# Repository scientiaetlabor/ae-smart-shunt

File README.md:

<h1 align="center">

  Ace's Electronics Pty Ltd  
  Smart Battery Shunt
</h1>

# Looking to get up and running?
- [Wiki - Quickstart Guide](../../wiki/Quickstart-Guide)

# Project Goals:
The overall goal of this project is to make a simple, robust and reliable Ssmart batery shunt to monitor voltage, current and power of a lithium battery, or battery system.

# Design goals:  
- Smallest form-factor possible while being able to handle large currents, upwards of 300A, without getting too hot
- Zero maintenance
- Allow the data to be accessed from an OLED gauge, via BLE or ESPNow

# Features
- **High-Precision Monitoring**: Measures battery voltage, current, and power, and calculates state-of-charge (SOC).
- **Persistent State**: Remembers battery capacity and calibration settings across power cycles.
- **ESP-NOW Broadcasting**: Transmits battery data wirelessly to other ESP devices.
- **Heartbeat LED**: A blinking LED provides a visual indication that the device is running.
- **Load Disconnect Control**: Includes an onboard MOSFET driver to disconnect the load in case of a fault.
- **Comprehensive Protection Suite**:
    - **Low-Voltage Disconnect**: Protects the battery from over-discharge. The device enters a low-power sleep mode, periodically waking to check if the battery has been recharged.
    - **Overcurrent Protection**: Disconnects the load if the current exceeds a configurable threshold.
    - **Short-Circuit Protection**: Uses the INA226's hardware alert pin for a fast-acting response to short circuits.
- **User-Configurable**: All protection parameters can be configured via the serial CLI.
- **In-Situ Calibration & Testing**: A guided CLI allows for accurate calibration and hardware verification without needing to re-flash the firmware.

# Commissioning
Before its first use, the smart shunt **must be calibrated**. The device will not be fully operational until this step is complete.
1.  Connect the device to a computer via USB.
2.  Open a serial monitor (e.g., the PlatformIO Serial Monitor) at **115200 baud**.
3.  Follow the on-screen prompts to run the calibration routines. You will be prompted to run the **Shunt Resistance Calibration (`r`)** first.
4.  Once calibration is complete, the device is ready for use.

# Serial Command-Line Interface (CLI)
The smart shunt is configured via a simple serial command-line interface. When connected, you can press a key followed by Enter to activate a command.

| Key | Command | Description |
|:---:|---|---|
| `c` | **Current Calibration** | Runs the guided multi-point current calibration routine. This maps the sensor's raw readings to true current values. |
| `r` | **Shunt Resistance Calibration** | Runs a routine to calculate the precise resistance of your shunt. **This must be run before first use.** |
| `p` | **Protection Settings** | Allows you to configure the thresholds for Low-Voltage Cutoff, Hysteresis, and Overcurrent Protection. |
| `l` | **Load Toggle** | Manually toggles the load disconnect MOSFET ON or OFF. Useful for testing the hardware circuit. |
| `a` | **Alert Toggle** | Toggles the hardware overcurrent alert ON or OFF. Useful for debugging. |
| `s` | **Status Display** | Displays the current protection settings, including the actual hardware alert threshold read from the INA226. |
| `d` | **Register Dump** | Prints the raw values of the INA226's key hardware registers for deep debugging. |

# v0.0.1
Version 0.0.1 has been prototyped. I will hand assemble some test boards and do some testing. ~ETA for completion is 10/8/25.

# Where to Buy:
TBA, but most likely will be vvailable to purchase in Australia or New Zealand via <a href="https://d1b959-f7.myshopify.com/">The AE Store</a>

## Support:
Contact me direct via ace<@>aceselectronics.com.au, just make it look like a normal email address. (hiding from the bots ;)

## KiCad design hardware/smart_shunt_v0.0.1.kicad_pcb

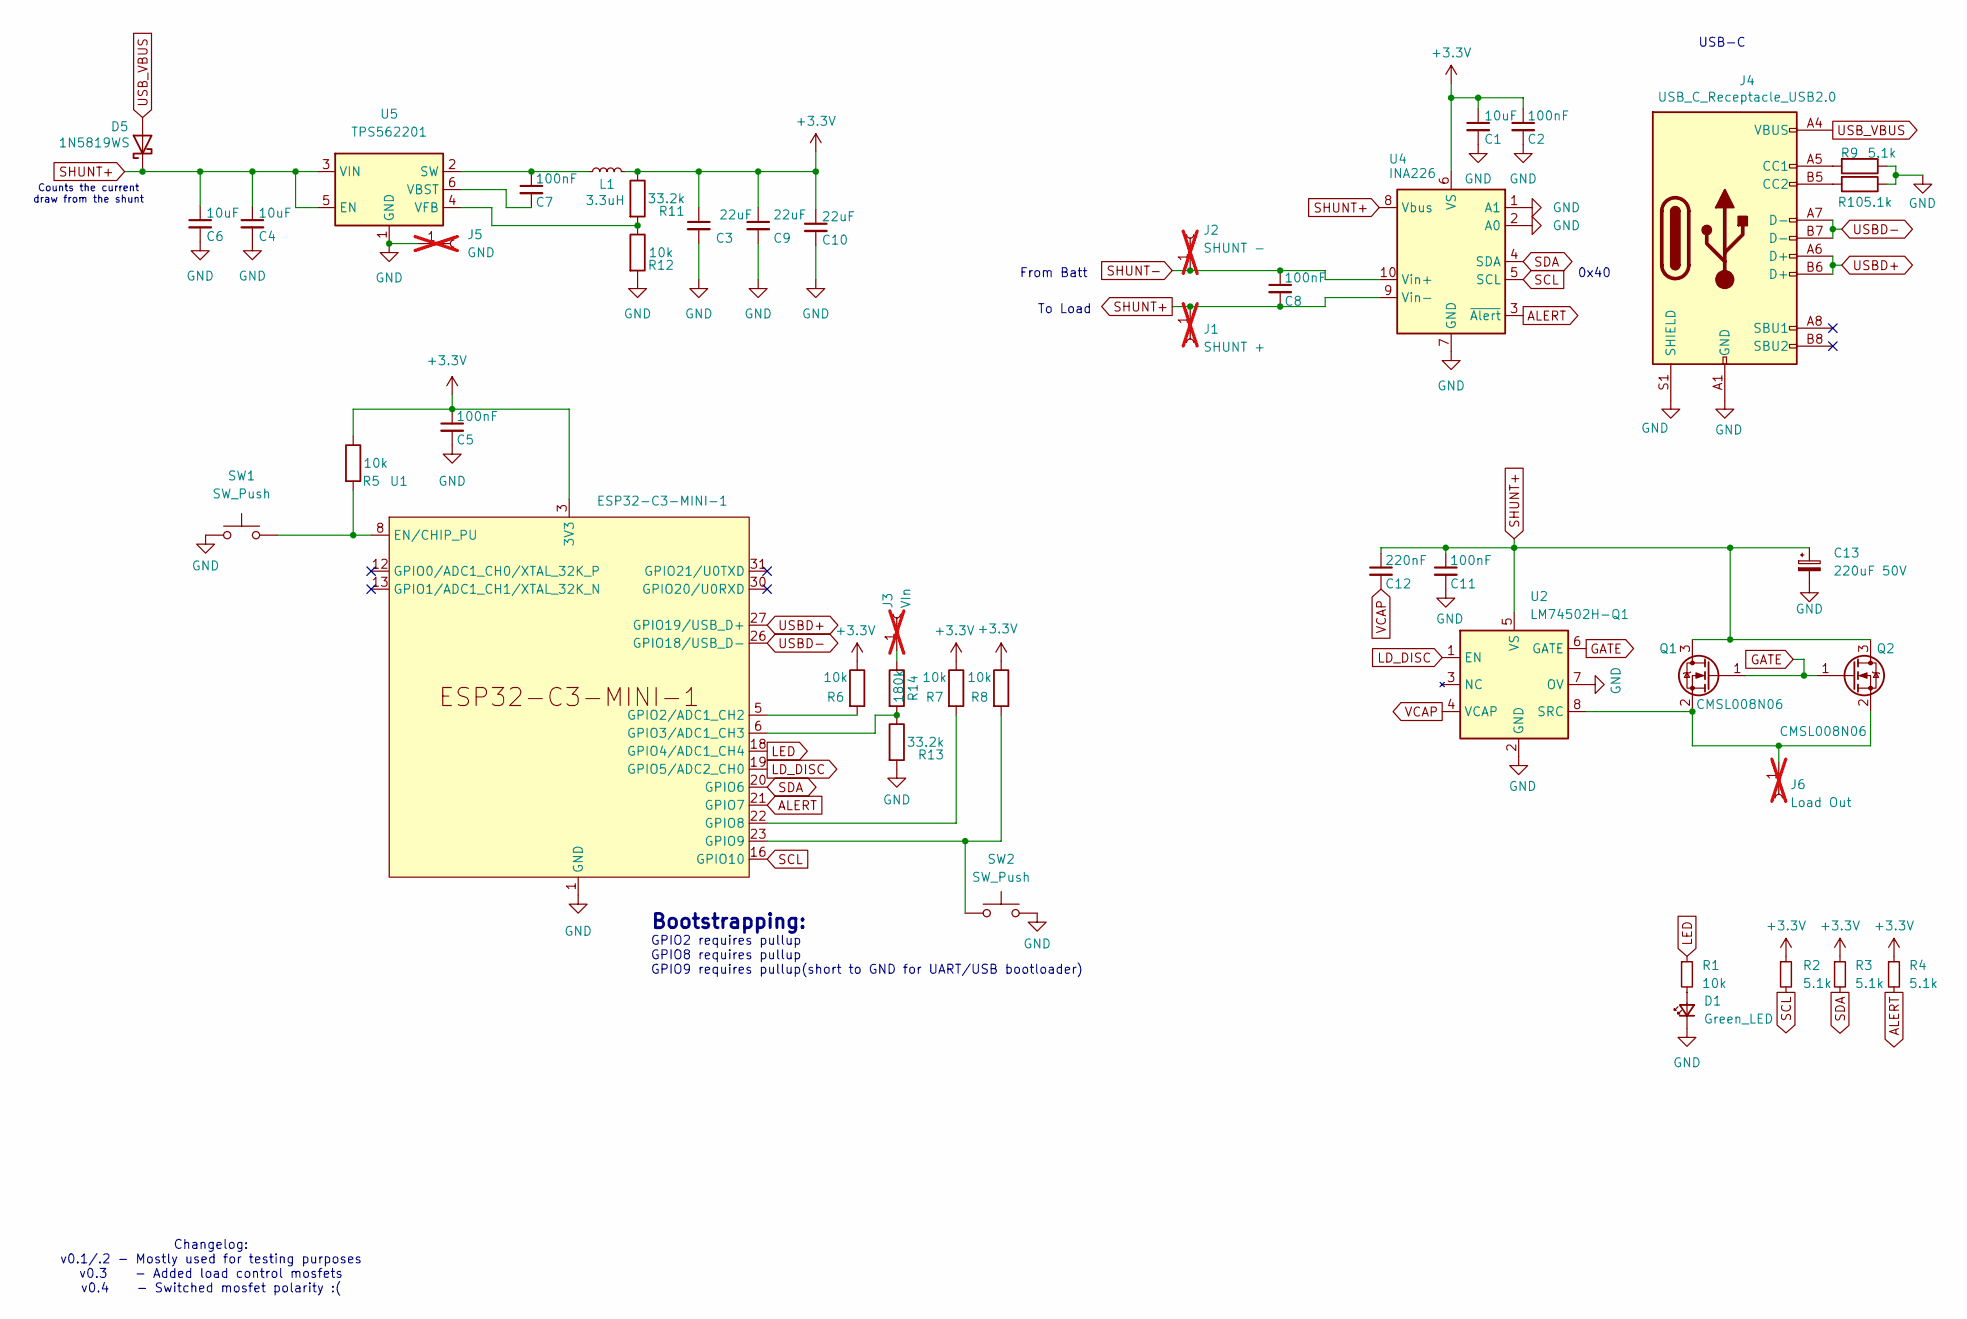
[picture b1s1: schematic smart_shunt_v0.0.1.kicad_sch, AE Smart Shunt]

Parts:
C1: 10uF; C_0603_1608Metric; MFR# CL10A106KP8NNNC; lcsc C19702
C2, C5, C7, C8, C11: 100nF; C_0603_1608Metric; MFR# CC0603KRX7R9BB104; lcsc C14663
C3, C9, C10: 22uF; C_0603_1608Metric; MFR# CL21A226MAQNNNE; lcsc C45783
C4, C6: 10uF; C_0805_2012Metric; MFR# GRM21BR6YA106KE43L; lcsc C162422
C12: 220nF; C_0805_2012Metric; MFR# CL21B224KBFNNNE; lcsc C5378
C13: 220uF 50V; CP_Elec_8x10.5; MFR# VP1H221M0810; lcsc C4054388
D1: Green_LED; LED_0402_1005Metric; MFR# SZYY0402YG; lcsc C434449
D5: 1N5819WS; D_SOD-323; MFR# 1N5819WS S4; lcsc C2927280
J1: SHUNT +; MountingHole_17mm; not fitted
J2: SHUNT -; MountingHole_17mm; not fitted
J3: VIn; MountingHole_3.2mm_M3_Pad_Via; not fitted
J4: USB_C_Receptacle_USB2.0; USB_C_Receptacle_GCT_USB4110; MFR# TYPE-C 16P QTWT; LCSC C5187472
J5: GND; MountingHole_3.2mm_M3_Pad_Via; not fitted
J6: Load Out; MountingHole_17mm; not fitted
L1: 3.3uH; L_APV_ANR4030; MFR# SWPA4030S3R3MT; lcsc C15269
Q1, Q2: CMSL008N06; MFR# CMSL008N06; lcsc C22364968
R1, R5, R6, R7, R8, R12: 10k; R_0603_1608Metric; MFR# 0603WAF1002T5E; lcsc C25804
R2, R3, R4, R9, R10: 5.1k; R_0603_1608Metric; MFR# 0603WAF5101T5E; lcsc C23186
R11, R13: 33.2k; R_0603_1608Metric; MFR# RMC060333.2K1%N; lcsc C325687
R14: 180k; R_0603_1608Metric; MFR# RC0603FR-07180KL; lcsc C123419
SW1, SW2: SW_Push; ALPSALPINE-SKSCLBE010_C115361; MFR# SKSCLBE010; lcsc C115361
U1: ESP32-C3-MINI-1; MFR# ESP32-C3-MINI-1-H4; lcsc C2934569
U2: LM74502H-Q1; SOT-23-8; MFR# TI LM74502HQDDFRQ1; lcsc C5219203
U4: INA226; VSSOP-10_3x3mm_P0.5mm; MFR# INA226AIDGSR; lcsc C49851
U5: TPS562201; SOT-23-6; MFR# TPS562201DDCR; lcsc C90061

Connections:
+3.3V: C1.1, C2.1, C3.1, C5.1, C9.1, C10.1, L1.2, R2.1, R3.1, R4.1, R5.1, R6.1, R7.1, R8.1, R11.1, U1.3 (3V3), U4.6 (VS)
ALERT: R4.2, U1.21 (GPIO7), U4.3 (~Alert)
GATE: Q1.1 (G), Q2.1 (G), U2.6 (GATE)
GND: C1.2, C2.2, C3.2, C4.2, C5.2, C6.2, C9.2, C10.2, C11.2, C13.2, D1.1 (K), J4.A1 (GND), J4.A12 (GND), J4.B1 (GND), J4.B12 (GND), J4.S1 (SHIELD), J5.1, R9.1, R10.1, R12.2, R13.2, SW1.2, SW2.2, U1.1 (GND), U1.2 (GND), U1.11 (GND), U1.14 (GND), U1.36 (GND), U1.37 (GND), U1.38 (GND), U1.39 (GND), U1.40 (GND), U1.41 (GND), U1.42 (GND), U1.43 (GND), U1.44 (GND), U1.45 (GND), U1.46 (GND), U1.47 (GND), U1.48 (GND), U1.49 (GND), U1.50 (GND), U1.51 (GND), U1.52 (GND), U1.53 (GND), U2.2 (GND), U2.7 (OV), U4.1 (A1), U4.2 (A0), U4.7 (GND), U5.1 (GND)
LD_DISC: U1.19 (GPIO5/ADC2_CH0), U2.1 (EN)
LED: R1.1, U1.18 (GPIO4/ADC1_CH4)
unnamed: D1.2 (A), R1.2
unnamed: J3.1, R14.1
unnamed: J4.A5 (CC1), R9.2
unnamed: J4.B5 (CC2), R10.2
unnamed: J6.1, Q1.2 (S), Q2.2 (S), U2.8 (SRC)
unnamed: R5.2, SW1.1, U1.8 (EN/CHIP_PU)
unnamed: R6.2, U1.5 (GPIO2/ADC1_CH2)
unnamed: R13.1, R14.2, U1.6 (GPIO3/ADC1_CH3)
unnamed: R7.2, U1.22 (GPIO8)
unnamed: R8.2, SW2.1, U1.23 (GPIO9)
unnamed: C7.1, L1.1, U5.2 (SW)
unnamed: C7.2, U5.6 (VBST)
unnamed: R11.2, R12.1, U5.4 (VFB)
SCL: R2.2, U1.16 (GPIO10), U4.5 (SCL)
SDA: R3.2, U1.20 (GPIO6), U4.4 (SDA)
SHUNT+: C4.1, C6.1, C8.2, C11.1, C12.1, C13.1, D5.1 (K), J1.1, Q1.3 (D), Q2.3 (D), U2.5 (VS), U4.8 (Vbus), U4.9 (Vin-), U5.3 (VIN), U5.5 (EN)
SHUNT-: C8.1, J2.1, U4.10 (Vin+)
USBD+: J4.A6 (D+), J4.B6 (D+), U1.27 (GPIO19/USB_D+)
USBD-: J4.A7 (D-), J4.B7 (D-), U1.26 (GPIO18/USB_D-)
USB_VBUS: D5.2 (A), J4.A4 (VBUS), J4.A9 (VBUS), J4.B4 (VBUS), J4.B9 (VBUS)
VCAP: C12.2, U2.4 (VCAP)

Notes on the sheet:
0x40
USB-C
From Batt
Counts the current draw from the shunt
Changelog: v0.1/.2 - Mostly used for testing purposes v0.3 - Added load control mosfets v0.4 - Switched mosfet polarity :(
To Load
Bootstrapping:
GPIO2 requires pullup GPIO8 requires pullup GPIO9 requires pullup(short to GND for UART/USB bootloader)

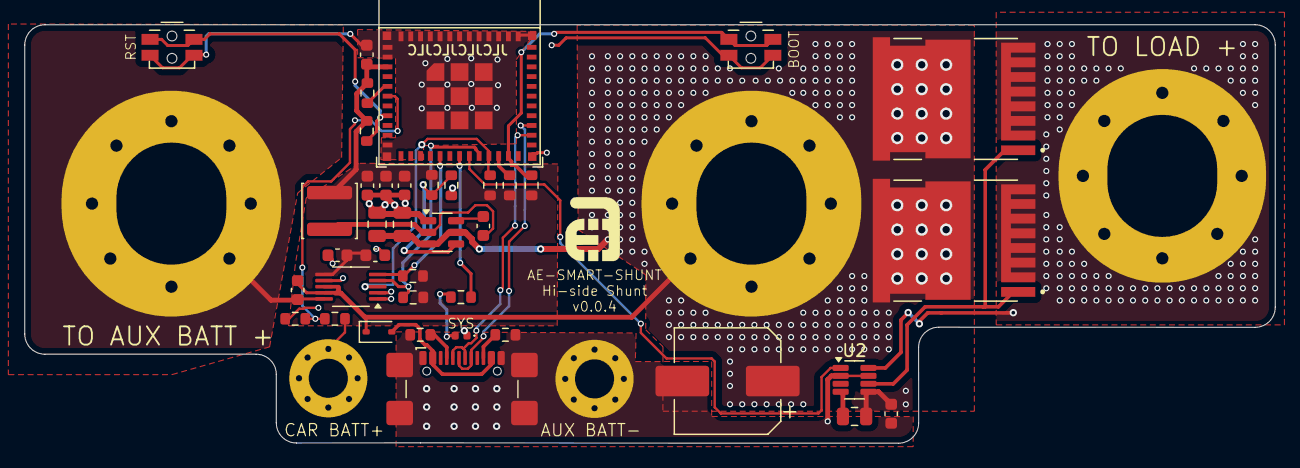
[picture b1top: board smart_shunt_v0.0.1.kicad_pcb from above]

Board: 2 copper layers, 102.4 x 34.3 mm, 44 parts (0 on the bottom side), 27 nets.

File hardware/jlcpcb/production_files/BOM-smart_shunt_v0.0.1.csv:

Comment,Designator,Footprint,LCSC,Quantity
SW_Push,"SW1,SW2",ALPSALPINE-SKSCLBE010_C115361,C115361,2
180k,R14,R_0603_1608Metric,C123419,1
100nF,"C11,C2,C5,C7,C8",C_0603_1608Metric,C14663,5
3.3uH,L1,L_APV_ANR4030,C15269,1
10uF,"C4,C6",C_0805_2012Metric,C15850,2
10uF,C1,C_0603_1608Metric,C19702,1
CMSL008N06,"Q1,Q2",CMSL008N06,C22364968,2
5.1k,"R10,R2,R3,R4,R9",R_0603_1608Metric,C23186,5
10k,"R1,R12,R5,R6,R7,R8",R_0603_1608Metric,C25804,6
ESP32-C3-MINI-1,U1,ESP32-C3-MINI-1,C2838502,1
1N5819WS,D5,D_SOD-323,C2927280,1
33.2k,"R11,R13",R_0603_1608Metric,C325687,2
Green_LED,D1,LED_0402_1005Metric,C401111,1
220uF 50V,C13,CP_Elec_8x10.5,C4054388,1
INA226,U4,VSSOP-10_3x3mm_P0.5mm,C49851,1
USB_C_Receptacle_USB2.0,J4,USB_C_Receptacle_GCT_USB4110,C5187472,1
LM74502H-Q1,U2,SOT-23-8,C5219203,1
220nF,C12,C_0805_2012Metric,C5378,1
22uF,"C10,C3,C9",C_0603_1608Metric,C59461,3
TPS562201,U5,SOT-23-6,C90061,1
SHUNT +,,MountingHole_17mm,,0
GND,,MountingHole_3.2mm_M3_Pad_Via,,0
SHUNT -,,MountingHole_17mm,,0
VIn,,MountingHole_3.2mm_M3_Pad_Via,,0
Load Out,,MountingHole_17mm,,0

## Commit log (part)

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2025-07-20 v0.0.1 off to JLCPCB
2025-07-20 cleaning up old files
2025-07-29 INA226 wip
2025-07-31 modifying project structure
2025-08-13 fixing RFT
2025-08-15 Updated RFT and calibration
2025-08-15 Fixing spaces
2025-08-16 feat: Add comprehensive test suite for firmware
    This change introduces a comprehensive test suite for the firmware.
    It adds a native test environment to allow for unit testing on a host machine.
    This required creating mocks for various Arduino and ESP-IDF libraries.
    The test suite covers:
    - Current, voltage, and power calculations.
    - Battery capacity and run-flat time calculations.
2025-08-16 feat: Add GitHub Actions workflow for CI
    This adds a GitHub Actions workflow to automatically run the native
    unit test suite on every push. This will help ensure code quality
    and prevent regressions.
2025-08-17 library updates
2025-08-17 feat: Add CI workflow for OTA releases
    This commit updates the CI workflow to automatically build the firmware and create a GitHub release when a new version tag is pushed.
    This is a necessary step for the OTA update functionality to work, as the device needs to download the `firmware.bin` from a GitHub release.
2025-08-17 Fixing ota stuff
2025-08-17 small fixes
2025-08-17 Testing OTA changes
2025-08-17 fixing missing variables
2025-08-17 Adding resistance calibration
2025-08-17 Changing logging
2025-08-29 v0.0.2 update, before FETs
2025-09-09 feat: Implement load protection and sleep features
    This commit introduces several new features to the smart shunt firmware:
    - **Load Disconnect Control:** The firmware can now control a load-disconnect MOSFET connected to GPIO5. The load is disconnected if the battery voltage or current go outside of user-defined ranges.
    - **Short-Circuit/Overcurrent Protection:** The INA226 alert pin, connected to GPIO7, is used to trigger an interrupt in case of a short circuit or overcurrent event. This provides a fast-acting prot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
    - **Low-Voltage Cutoff with Deep Sleep:** When the battery voltage drops below a configurable threshold, the load is di
2025-09-09 fix: Prevent deep sleep on USB power
    This commit fixes an issue where the device would enter deep sleep when powered from USB for setup, due to the low voltage protection being triggered by a low voltage reading when no battery is conne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
    The `checkAndHandleProtection` function is modified to bypass the low-voltage protection logic if the measured voltage is below 5.25V.
    A new unit test is added to verify this behavior.
2025-09-09 fix: Refactor alert handling and fix tests
    This commit fixes several issues with the protection features:
    - **ISR Watchdog Timeout:** The INA226 alert handling has been refactored to prevent a watchdog timeout. The Interrupt Service Routine (ISR) now only sets a volatile flag. The main loop checks this f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
    - **Test Logic:** The unit test for the alert disconnect (`test_alert_disconnect`) has been corrected to accurately reflect the new ISR-and-main-loop interaction. It now simulates the ISR setting the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
2025-09-09 fix: Prevent alert spam when load is disconnected
    This commit fixes an issue where the INA226 alert would continuously
    trigger and flood the serial log if the alert condition persisted after
    the load was disconnected.
    The `processAlert` function is modified to only take action (print a
    message and disconnect the load) if the load is currently connected. If
    an alert is received while the load is already disconnected, the alert
2025-09-09 feat: Add commissioning check on startup
    This commit introduces a commissioning check to ensure the device is not
    used before it has been configured.
    The device is now considered "configured" only after the shunt
    resistance has been successfully calibrated and saved to NVS at least
    once.
    If the device boots up in an unconfigured state, it will:
2025-09-09 fix: Resolve compilation error from name conflict
    This commit fixes a compilation error caused by a member variable and a
    member function both being named `isConfigured`.
    The member variable has been renamed to `m_isConfigured` to resolve the
    conflict. All uses of the variable have been updated to the new name.
2025-09-09 fix: Improve calibration live stream UI
    This commit improves the user experience of the live debug stream during
    the calibration process.
    The `Serial.printf` call that prints the live data now uses a carriage
    return (`\r`) instead of a newline (`\n`). This causes the output to
    overwrite itself on a single line, preventing the calibration step
    instructions from scrolling off the screen.
2025-09-09 fix: Add robust check for device configuration
    This commit fixes a bug where the "device not configured" reminder was
    not being displayed on first boot.
    The `loadShuntResistance` function has been made more robust. It now
    explicitly checks for the existence of the `ina_cal` NVS namespace and
    the `cal_ohms` key before considering the device configured.
    This ensures that on a fresh device, the `isConfigured` flag is
2025-09-09 refactor: Improve calibration by using zero-load point
    This commit refactors the current calibration routine to improve its
    accuracy and robustness, addressing user feedback.
    The previous method of measuring a separate self-consumption offset and
    subtracting it from readings was flawed. The new implementation follows
    a more standard multi-point calibration procedure:
    1. The calibration process now starts with a true "zero external load"
2025-09-09 feat: Add heartbeat LED, load toggle, and interactive tests
    This commit introduces several new features to improve device feedback
    and testing capabilities:
    1. **Heartbeat LED**: The onboard LED on GPIO4 now blinks every 500ms
    to provide a constant visual indication that the device firmware is
    running.
    2. **Manual Load Toggle**: A new 'l' command has been added to the CLI
2025-09-09 feat: Use whole-number targets in calibration routine
    This commit improves the usability of the current calibration routine
    by adjusting the set points to use whole numbers.
    The underlying percentage vector has been modified so that for common
    shunt ratings (e.g., 50A, 100A), the resulting target currents
    are simple whole numbers (e.g., 1A, 2A, 5A), making the process
    easier for the user to follow.
2025-09-09 feat: Implement comprehensive shunt protection and usability features
    This commit introduces a wide range of new features and improvements to
    the smart shunt firmware, turning it into a much more robust and
    user-friendly device.
    Major features include:
    1. **Load Protection & Disconnect**:
    * The firmware now actively controls a load disconnect MOSFET.
2025-09-09 chore: Add debugging for MOSFET control
    This commit adds verbose serial printing to the `setLoadConnected`
    function to help diagnose an issue where the load disconnect toggle is
    not working as expected.
    This is a temporary change to gather more information from the hardware
    and will be reverted before the final fix is committed.
2025-09-09 docs: Update README with new features and usage
    This commit significantly updates the main README.md file to document
    all the new features and functionality that have been added to the
    firmware.
    The new sections include:
    - **Features**: A high-level overview of the smart shunt's
    capabilities, including the new protection suite.
2025-09-09 feat: Add calibration export and extrapolation
    This commit introduces two major improvements to the calibration
    process based on user feedback:
    1. **Calibration Data Export**: A new 'e' command has been added to the
    CLI. This command allows the user to export the stored multi-point
    calibration data for a given shunt rating. The data is printed to
    the serial console formatted as a C++ vector, which can be easily
2025-09-10 feat: Add keyboard toggle for hardware overcurrent alert
    Introduces a keyboard command ('a') to toggle the INA226 hardware overcurrent alert on and off.
    This allows the user to disable the immediate load disconnect feature for testing and debugging purposes, as requested.
    The implementation includes:
    - A new flag `m_hardwareAlertsDisabled` in the `INA226_ADC` class.
    - A `toggleHardwareAlerts()` method to flip the state.
    - Modified `configureAlert()` to enable/disable the alert on the INA226 chip.
2025-09-10 feat: Add serial command to display protection status
    Introduces a new 's' command in the serial CLI to display the current protection settings.
    This allows the user to easily check the configured values for:
    - Hardware Alert Status (ENABLED/DISABLED)
    - Overcurrent Threshold
    - Low Voltage Cutoff
    - Hysteresis
2025-09-10 feat: Add alert pin state to status command
    Adds the live digital state of the INA_ALERT_PIN to the 's' status screen output.
    This provides more detailed diagnostic information to help understand why the hardware alert might be triggering. The output now shows both the raw pin state (HIGH/LOW) and a user-friendly interpreta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
2025-09-10 fix: Correct alert limit calculation in INA226_WE library
    This commit fixes a critical bug in the third-party INA226_WE library where the conversion factor for setting the shunt voltage alert limit was incorrect by a factor of 1000.
    The calculation was changed from `limit * 400` to `limit * 400000` for both SHUNT_OVER and SHUNT_UNDER alert types.
    This resolves the issue where the hardware overcurrent alert was triggering at a much lower threshold than configured, causing the load to disconnect immediately.
    This commit also includes the diagnostic tools developed to find this bug:
    - 'a' command to toggle hardware alerts.
    - 's' command to display protection status, including the actual hard
2025-09-10 docs: Update README with new CLI commands
    Adds the new 'a' (toggle alerts) and 's' (display status) commands to the Serial Command-Line Interface table in the README.md file.
    This ensures the documentation is up-to-date with the latest features.
2025-09-10 fix: Enable load output during calibration routines
    This commit fixes a workflow issue where the calibration routines (`r` and `c`) could not be run on an uncalibrated device.
    Previously, an uncalibrated device would disable the load output on boot as a safety measure. However, the calibration routines required the load to be enabled to apply a test current, but did not en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
    This change adds a call to `setLoadConnected(true, MANUAL)` at the beginning of both `runShuntResistanceCalibration` and `runCurrentCalibrationMenu` to ensure the load is enabled, allowing the calibr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
2025-09-10 feat: Add command to dump INA226 registers
    Introduces a new 'd' command in the serial CLI to print the raw, hexadecimal values of the INA226's key hardware registers.
    This provides a powerful tool for deep debugging of the chip's configuration state, allowing for a direct comparison between the software's intended state and the hardware's actual state.
    The following registers are dumped:
    - Configuration (0x00)
    - Calibration (0x05)
    - Mask/Enable (0x06)
2025-09-10 Fixing reversed MOSFETs
2025-09-10 Fixing ADC trace - Thanks Vincent!
